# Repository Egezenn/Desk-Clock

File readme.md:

# Desk Clock

Simple desk clock that displays date&time.

## Software

### KiCad

Designed with DIY PCB production methods in mind. Has DS1302 symbol&footprint that I could've just used pin headers, didn't, ¯\\\_(ツ)\_/¯.

### Proteus

To test, link the compiled hex file to PIC16F877A component.

### CCS C Compiler

Compile contents of [src](src) with the compiler.

## Components

- PIC16F877a
- 1602 LCD
- DS1302
- 4mHz crystal oscillator (only one that was in stock, shouldn't matter all that much)
- 4x buttons (dual, because I already had them)
- 2x 22pF ceramic disc capacitor
- 6x 10k ohm resistors
- 5V power source
- CR2032 lithium battery (for DS1302)

## Acknowledgements of stuff that could've been better section

- Usage of a more reliable RTC module like DS1307
- A smaller & cheaper PIC, PIC16F877A is a bit of an overkill here (school project ¯\\\_(ツ)\_/¯)
- Interrupt section of the C source file could've been condensed via functions and whatnot
- `day_in_week` could also be displayed, there's space for it in the LCD

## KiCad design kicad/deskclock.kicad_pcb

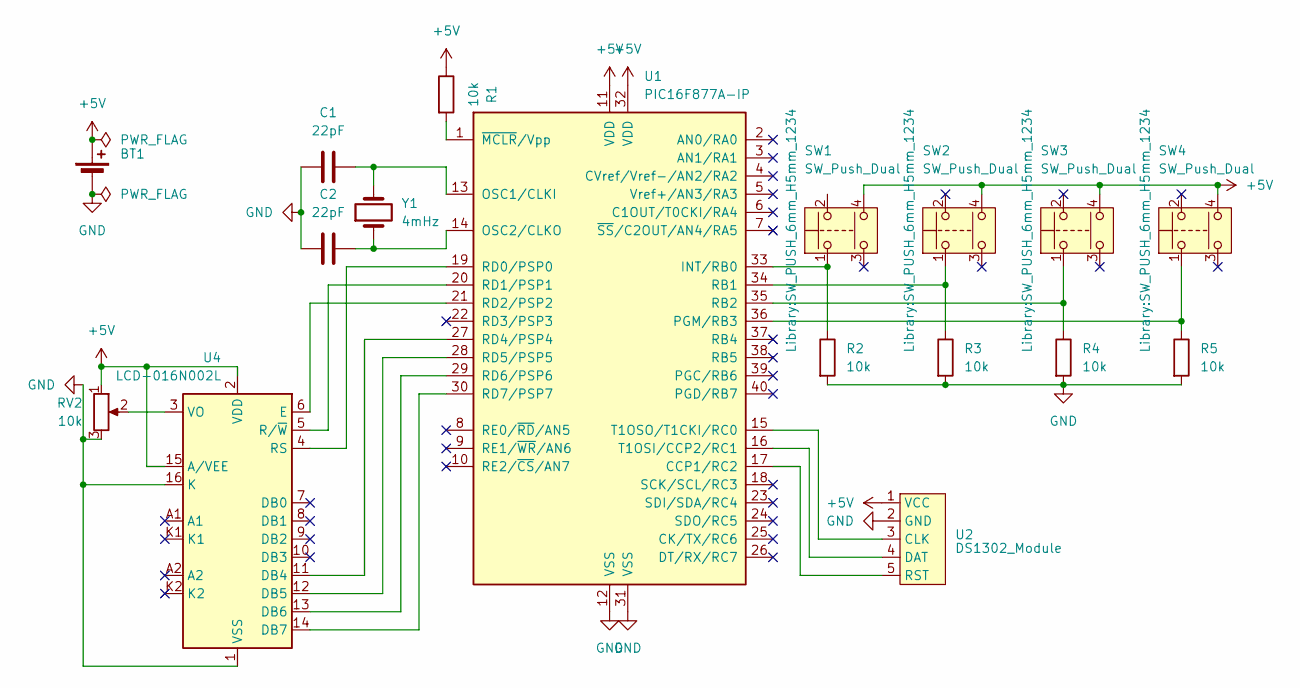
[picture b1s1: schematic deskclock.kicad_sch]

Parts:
BT1: TerminalBlock_4Ucon_1x02_P3.50mm_Horizontal
C1, C2: 22pF; C_Disc_D3.0mm_W1.6mm_P2.50mm
R1, R2, R3, R4, R5: 10k; R_Axial_DIN0207_L6.3mm_D2.5mm_P10.16mm_Horizontal
RV2: 10k; Potentiometer_Bourns_3386F_Vertical
SW1, SW2, SW3, SW4: SW_Push_Dual; SW_PUSH_6mm_H5mm_1234
U1: PIC16F877A-IP; DIP-40_W15.24mm
U2: DS1302_Module; ds1302
U4: LCD-016N002L
Y1: 4mHz; Crystal_HC49-U_Vertical

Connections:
+5V: BT1.1 (+), R1.1, RV2.1, SW1.4, SW2.4, SW3.4, SW4.4, U1.11 (VDD), U1.32 (VDD), U2.1 (VCC), U4.2 (VDD), U4.15 (A/VEE)
GND: BT1.2 (-), C1.1, C2.1, R2.2, R3.2, R4.2, R5.2, RV2.3, U1.12 (VSS), U1.31 (VSS), U2.2 (GND), U4.1 (VSS), U4.16 (K)
unnamed: U1.17 (CCP1/RC2), U2.5 (RST)
unnamed: R2.1, SW1.1, U1.33 (INT/RB0)
unnamed: C1.2, U1.13 (OSC1/CLKI), Y1.2
unnamed: C2.2, U1.14 (OSC2/CLKO), Y1.1
unnamed: R5.1, SW4.1, U1.36 (PGM/RB3)
unnamed: R3.1, SW2.1, U1.34 (RB1)
unnamed: R4.1, SW3.1, U1.35 (RB2)
unnamed: U1.19 (RD0/PSP0), U4.4 (RS)
unnamed: U1.20 (RD1/PSP1), U4.5 (R/~W)
unnamed: U1.21 (RD2/PSP2), U4.6 (E)
unnamed: U1.27 (RD4/PSP4), U4.11 (DB4)
unnamed: U1.28 (RD5/PSP5), U4.12 (DB5)
unnamed: U1.29 (RD6/PSP6), U4.13 (DB6)
unnamed: U1.30 (RD7/PSP7), U4.14 (DB7)
unnamed: U1.16 (T1OSI/CCP2/RC1), U2.4 (DAT)
unnamed: U1.15 (T1OSO/T1CKI/RC0), U2.3 (CLK)
unnamed: R1.2, U1.1 (~MCLR/Vpp)
unnamed: RV2.2, U4.3 (VO)

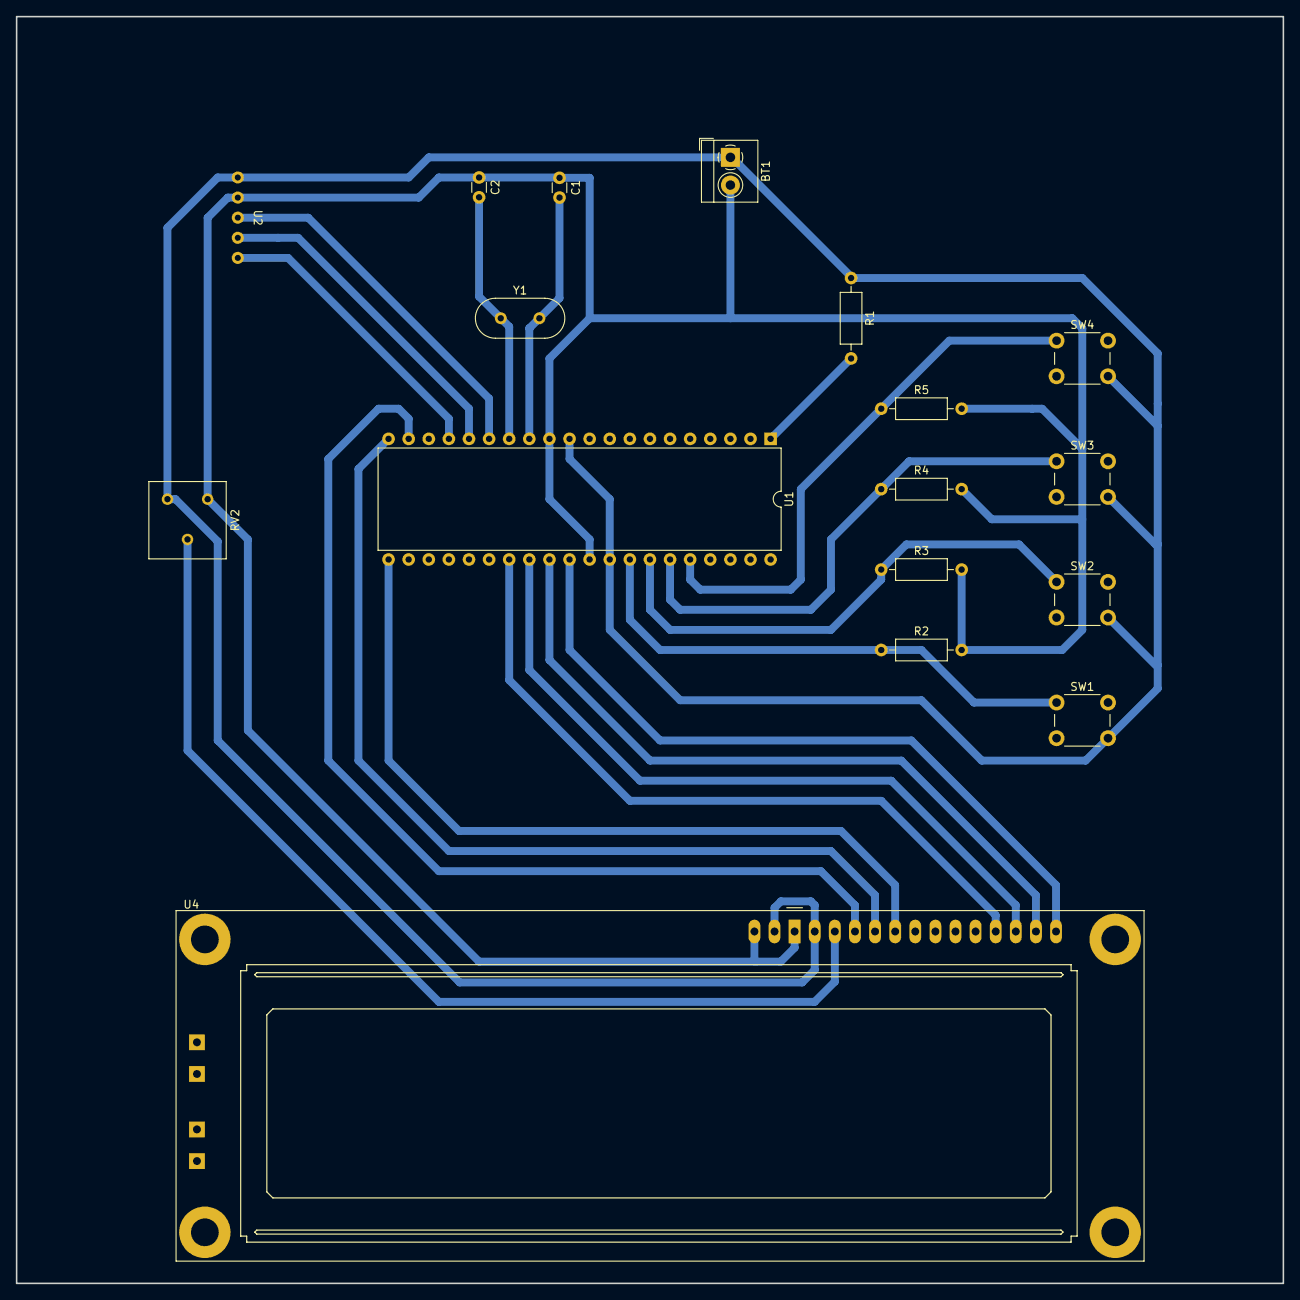
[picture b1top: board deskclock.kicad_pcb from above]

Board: 2 copper layers, 160.0 x 160.0 mm, 17 parts (0 on the bottom side), 20 nets.

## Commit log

2025-03-15 initial
2025-03-20 Create LICENSE
2025-04-16 Fix forgotten macros
